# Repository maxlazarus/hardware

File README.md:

#<a href="http://OpenRobotics.ca">OpenRobotics</a> electrical hardware repository<br>
Any questions please contact me at me max.prokopenko@gmail.com<br>
###Organization of this repo<br>
&nbsp;&nbsp;<a href="../../tree/master/Datasheets/">**Datasheets/**</a> Information regarding various components used in our devices<br>
&nbsp;&nbsp;<a href="../../tree/master/Documents/">**Documents/**</a> Reference documents and other useful guides<br>
&nbsp;&nbsp;<a href="../../tree/master/Libraries/">**Libraries/**</a> Device symbols and footprints for electical CAD programs, old ones are in Altium formats, using KiCad going forward<br>
&nbsp;&nbsp;<a href="../../tree/master/Projects/">**Projects/**</a> Contains subfolders, each one dedicated to a single project<br>
&nbsp;&nbsp;<a href="../../tree/master/Training/">**Training/**</a> Training modules developed by OpenRobotics members<br>

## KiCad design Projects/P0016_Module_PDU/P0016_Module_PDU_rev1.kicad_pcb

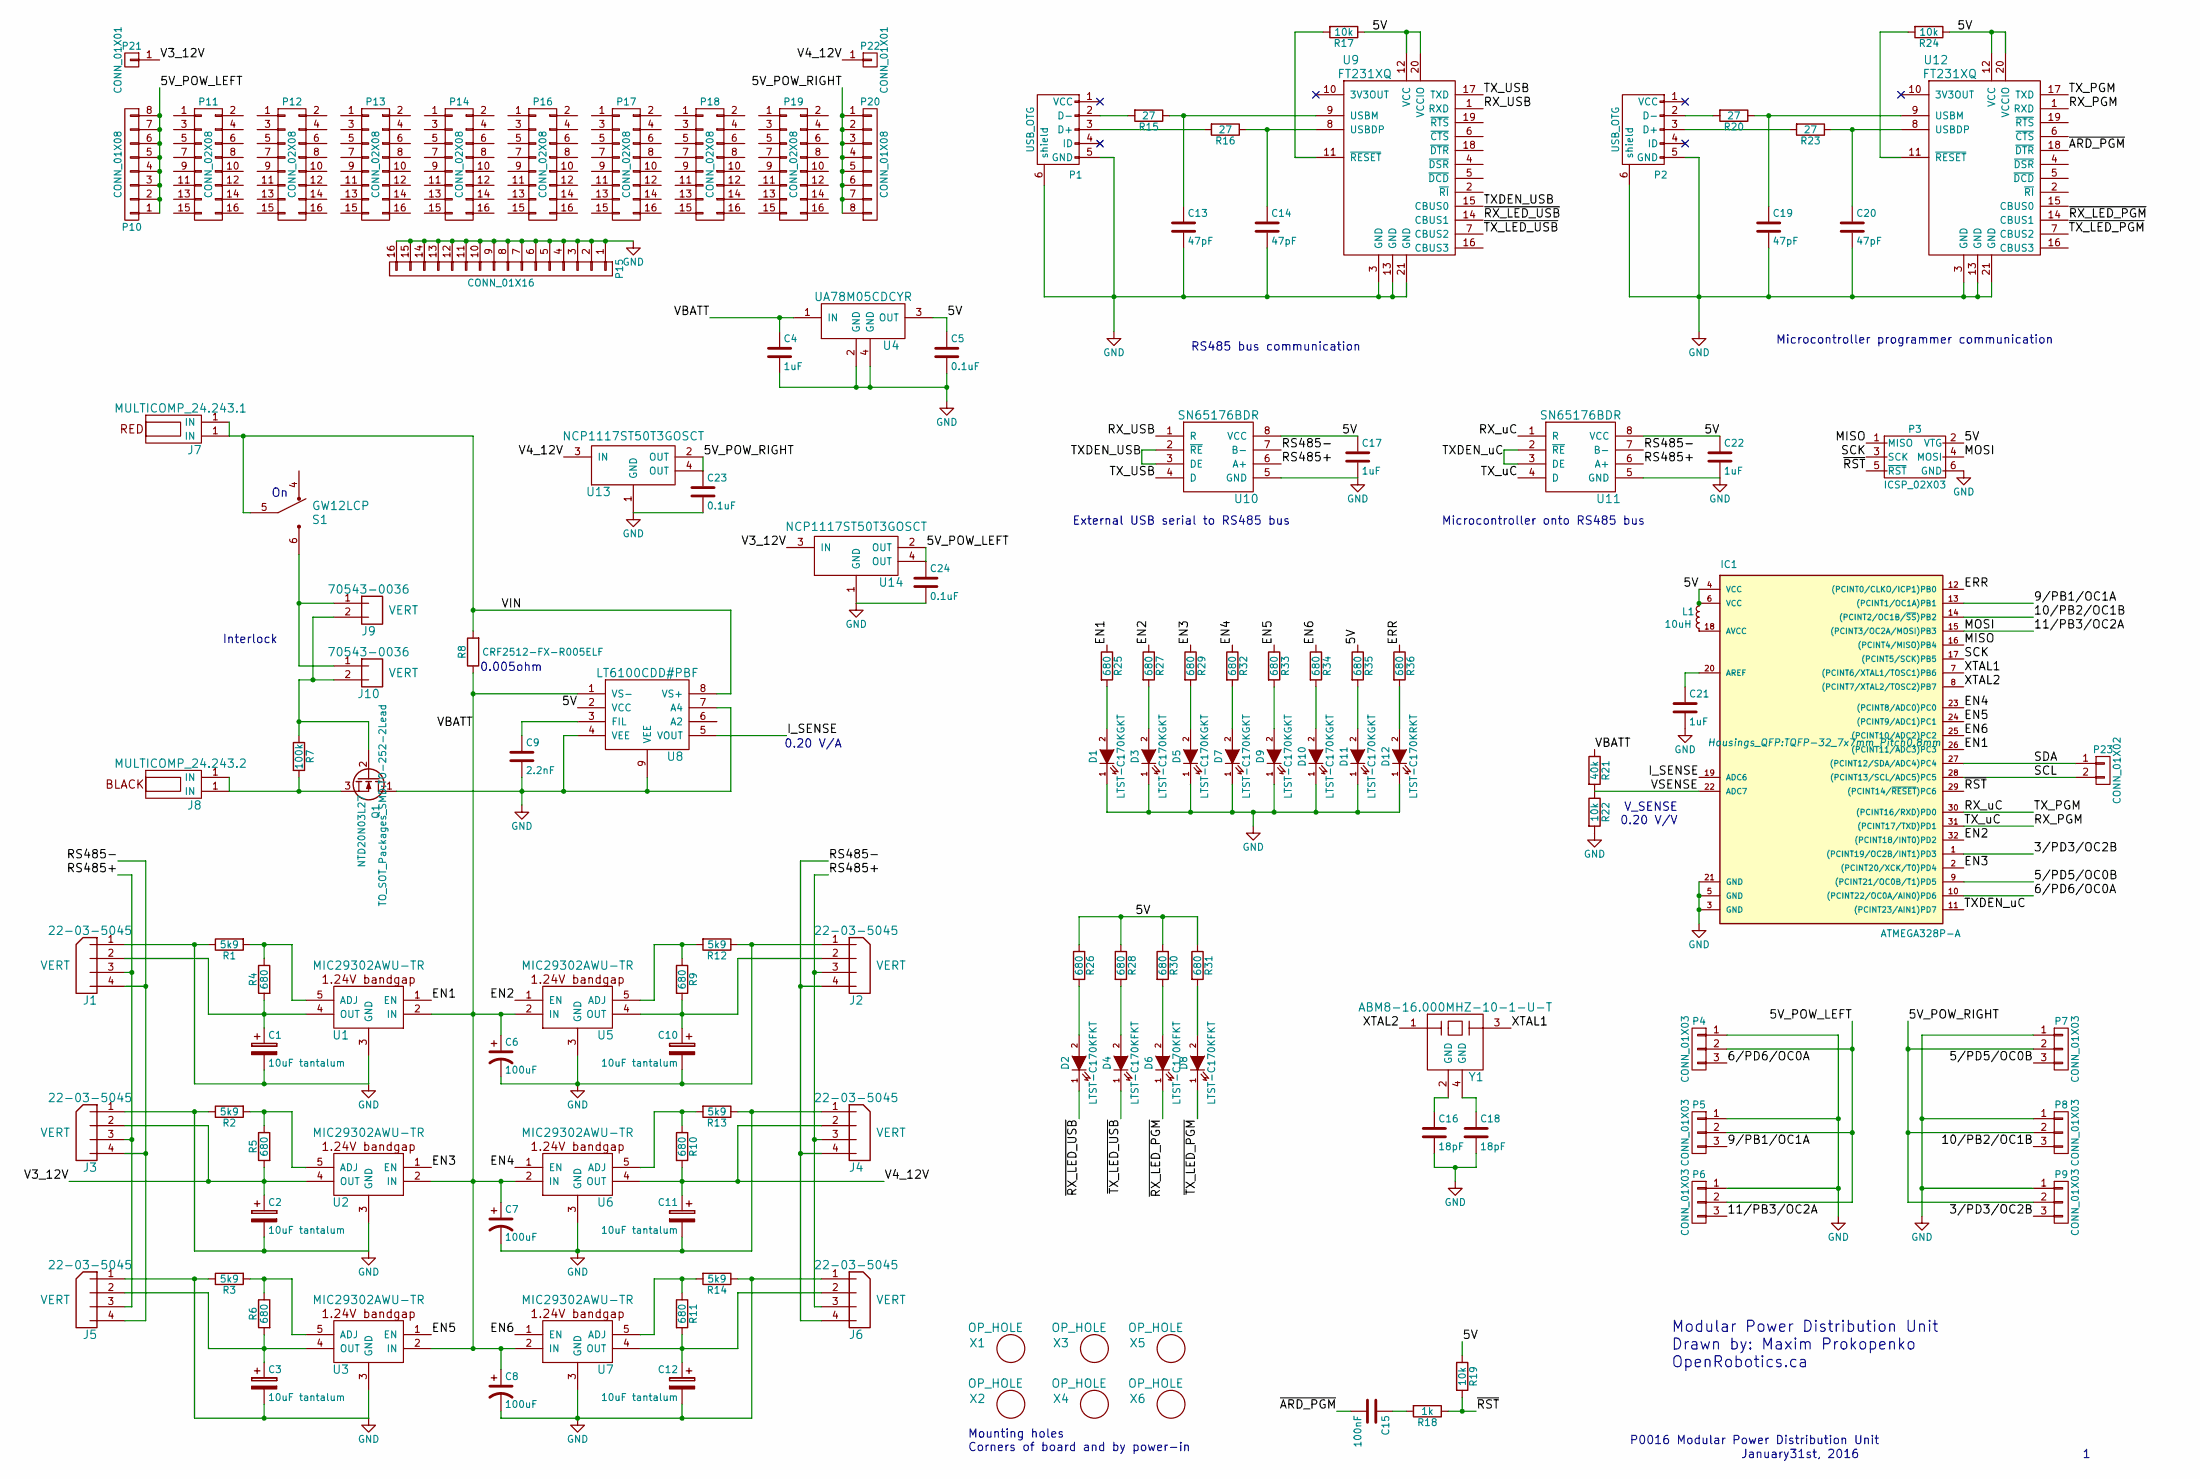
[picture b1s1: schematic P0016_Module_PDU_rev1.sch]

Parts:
C1, C2, C3, C10, C11, C12: 10uF tantalum; c_elec_5x4.5
C4, C17, C21, C22: 1uF; C_0805
C5, C23, C24: 0.1uF; C_0805
C6, C7, C8: 100uF; c_elec_5x4.5
C9: 2.2nF; C_0805
C13, C14, C19, C20: 47pF; C_0805
C15: 100nF; C_0805
C16, C18: 18pF; C_0805
D1, D3, D5, D7, D9, D10, D11: LTST-C170KGKT; LED_0805
D2, D4, D6, D8: LTST-C170KFKT; LED_0805
D12: LTST-C170KRKT; LED_0805
IC1: ATMEGA328P-A; TQFP-32_7x7mm_Pitch0.8mm
J1, J2, J3, J4, J5, J6: 22-03-5045; Pin_Header_Straight_1x04
J7: MULTICOMP_24.243.1; MULTICOMP_4MM_JACK
J8: MULTICOMP_24.243.2; MULTICOMP_4MM_JACK
J9, J10: 70543-0036; Pin_Header_Straight_1x02
L1: 10uH; C_0603
P1, P2: USB_OTG; USB_Micro-B_10103594-0001LF
P3: ICSP_02X03; Pin_Header_Straight_2x03
P4, P5, P6, P7, P8, P9: CONN_01X03; Pin_Header_Straight_1x03
P10, P20: CONN_01X08; Pin_Header_Straight_1x08
P11, P12, P13, P14, P16, P17, P18, P19: CONN_02X08; Pin_Header_Straight_2x08
P15: CONN_01X16; Pin_Header_Straight_1x16
P21, P22: CONN_01X01; Pin_Header_Straight_1x01
P23: CONN_01X02; Pin_Header_Straight_1x02
Q1: NTD20N03L27; TO-252-2Lead
R1, R2, R3, R12, R13, R14: 5k9; R_0603
R4, R5, R6, R9, R10, R11, R25, R26, R27, R28, R29, R30, R31, R32, R33, R34, R35, R36: 680; R_0603
R7: 100k; R_0603
R8: CRF2512-FX-R005ELF; R_2512
R15, R16, R20, R23: 27; R_0603
R17, R19, R22, R24: 10k; R_0603
R18: 1k; R_0603
R21: 40k; R_0603
S1: GW12LCP; GW12LCP_SWITCH_SPDT
U1, U2, U3, U5, U6, U7: MIC29302AWU-TR; TO-263-5Lead
U4: UA78M05CDCYR; SOT-223
U8: LT6100CDD#PBF; DFN-8-1EP_3x3mm_Pitch0.5mm
U9, U12: FT231XQ; QFN-20-1EP_4x4mm_Pitch0.5mm
U10, U11: SN65176BDR; SOIC-8_3.9x4.9mm_Pitch1.27mm
U13, U14: NCP1117ST50T3GOSCT; SOT-223
X1, X2, X3, X4, X5, X6: OP_HOLE; modular8_mounting_hole
Y1: ABM8-16.000MHZ-10-1-U-T; CSMD-ABM8

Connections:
/3/PD3/OC2B: IC1.1 ((PCINT19/OC2B/INT1)PD3), P9.3
/5/PD5/OC0B: IC1.9 ((PCINT21/OC0B/T1)PD5), P7.3
/5V: C5.1, C17.1, C22.1, IC1.4 (VCC), IC1.6 (VCC), L1.1, P3.2 (VTG), R17.1, R19.1, R24.1, R26.1, R28.1, R30.1, R31.1, R35.1, U4.3 (OUT), U8.2 (VCC), U9.12 (VCC), U9.20 (VCCIO), U10.8 (VCC), U11.8 (VCC), U12.12 (VCC), U12.20 (VCCIO)
/5V_POW_LEFT: C24.1, P4.2, P5.2, P6.2, P10.1, P10.2, P10.3, P10.4, P10.5, P10.6, P10.7, P10.8, U14.2 (OUT), U14.4 (OUT)
/5V_POW_RIGHT: C23.1, P7.2, P8.2, P9.2, P20.1, P20.2, P20.3, P20.4, P20.5, P20.6, P20.7, P20.8, U13.2 (OUT), U13.4 (OUT)
/6/PD6/OC0A: IC1.10 ((PCINT22/OC0A/AIN0)PD6), P4.3
/9/PB1/OC1A: IC1.13 ((PCINT1/OC1A)PB1), P5.3
/10/PB2/OC1B: IC1.14 ((PCINT2/OC1B/~SS~)PB2), P8.3
/11/PB3/OC2A: IC1.15 ((PCINT3/OC2A/MOSI)PB3), P3.4 (MOSI), P6.3
/EN1: IC1.26 ((PCINT11/ADC3)PC3), R25.1, U1.1 (EN)
/EN2: IC1.32 ((PCINT18/INT0)PD2), R27.1, U5.1 (EN)
/EN3: IC1.2 ((PCINT20/XCK/T0)PD4), R29.1, U2.1 (EN)
/EN4: IC1.23 ((PCINT8/ADC0)PC0), R32.1, U6.1 (EN)
/EN5: IC1.24 ((PCINT9/ADC1)PC1), R33.1, U3.1 (EN)
/EN6: IC1.25 ((PCINT10/ADC2)PC2), R34.1, U7.1 (EN)
/ERR: IC1.12 ((PCINT0/CLKO/ICP1)PB0), R36.1
/I_SENSE: IC1.19 (ADC6), U8.5 (VOUT)
/MISO: IC1.16 ((PCINT4/MISO)PB4), P3.1 (MISO)
/RS485+: J1.3, J2.3, J3.3, J4.3, J5.3, J6.3, U10.6 (A+), U11.6 (A+)
/RS485-: J1.4, J2.4, J3.4, J4.4, J5.4, J6.4, U10.7 (B-), U11.7 (B-)
/RX_PGM: IC1.31 ((PCINT17/TXD)PD1), U11.4 (D), U12.1 (RXD)
/RX_USB: U9.1 (RXD), U10.1 (R)
/RX_uC: IC1.30 ((PCINT16/RXD)PD0), U11.1 (R), U12.17 (TXD)
/SCK: IC1.17 ((PCINT5/SCK)PB5), P3.3 (SCK)
/SCL: IC1.28 ((PCINT13/SCL/ADC5)PC5), P23.2
/SDA: IC1.27 ((PCINT12/SDA/ADC4)PC4), P23.1
/TXDEN_USB: U9.15 (CBUS0), U10.2 (~RE), U10.3 (DE)
/TXDEN_uC: IC1.11 ((PCINT23/AIN1)PD7), U11.2 (~RE), U11.3 (DE)
/TX_USB: U9.17 (TXD), U10.4 (D)
/V3_12V: C2.1, J3.2, P21.1, R5.2, U2.4 (OUT), U14.3 (IN)
/V4_12V: C11.1, J4.2, P22.1, R10.2, U6.4 (OUT), U13.3 (IN)
/VBATT: C4.1, C6.1, C7.1, C8.1, R8.1, R21.1, U1.2 (IN), U2.2 (IN), U3.2 (IN), U4.1 (IN), U5.2 (IN), U6.2 (IN), U7.2 (IN), U8.1 (VS-)
/VIN: J7.1, R8.2, S1.5, U8.8 (VS+)
/VSENSE: IC1.22 (ADC7), R21.2, R22.1
/XTAL1: IC1.7 ((PCINT6/XTAL1/TOSC1)PB6), Y1.3
/XTAL2: IC1.8 ((PCINT7/XTAL2/TOSC2)PB7), Y1.1
/~ARD_PGM: C15.2, U12.18 (~DTR)
/~RST: IC1.29 ((PCINT14/~RESET~)PC6), P3.5 (~RST), R18.1, R19.2
/~RX_LED_PGM: D6.1 (K), U12.14 (CBUS1)
/~RX_LED_USB: D2.1 (K), U9.14 (CBUS1)
/~TX_LED_PGM: D8.1 (K), U12.7 (CBUS2)
/~TX_LED_USB: D4.1 (K), U9.7 (CBUS2)
GND: C1.2, C2.2, C3.2, C4.2, C5.2, C6.2, C7.2, C8.2, C9.2, C10.2, C11.2, C12.2, C13.2, C14.2, C16.2, C17.2, C18.2, C19.2, C20.2, C21.2, C22.2, C23.2, C24.2, D1.1 (K), D3.1 (K), D5.1 (K), D7.1 (K), D9.1 (K), D10.1 (K), D11.1 (K), D12.1 (K), IC1.3 (GND), IC1.5 (GND), IC1.21 (GND), J1.1, J2.1, J3.1, J4.1, J5.1, J6.1, P1.5 (GND), P1.6 (shield), P2.5 (GND), P2.6 (shield), P3.6 (GND), P4.1, P5.1, P6.1, P7.1, P8.1, P9.1, P15.1, P15.2, P15.3, P15.4, P15.5, P15.6, P15.7, P15.8, P15.9, P15.10, P15.11, P15.12, P15.13, P15.14, P15.15, P15.16, Q1.1 (D), R1.1, R2.1, R3.1, R12.1, R13.1, R14.1, R22.2, U1.3 (GND), U2.3 (GND), U3.3 (GND), U4.2 (GND), U4.4 (GND), U5.3 (GND), U6.3 (GND), U7.3 (GND), U8.4 (VEE), U8.7 (A4), U8.9 (VEE), U9.3 (GND), U9.13 (GND), U9.21 (GND), U10.5 (GND), U11.5 (GND), U12.3 (GND), U12.13 (GND), U12.21 (GND), U13.1 (GND), U14.1 (GND)
unnamed: C1.1, J1.2, R4.2, U1.4 (OUT)
unnamed: C3.1, J5.2, R6.2, U3.4 (OUT)
unnamed: C9.1, U8.3 (FIL)
unnamed: C10.1, J2.2, R9.2, U5.4 (OUT)
unnamed: C12.1, J6.2, R11.2, U7.4 (OUT)
unnamed: C13.1, R15.1, U9.9 (USBM)
unnamed: C14.1, R16.1, U9.8 (USBDP)
unnamed: C15.1, R18.2
unnamed: C16.1, Y1.2 (GND)
unnamed: C18.1, Y1.4 (GND)
unnamed: C19.1, R20.1, U12.9 (USBM)
unnamed: C20.1, R23.1, U12.8 (USBDP)
unnamed: C21.1, IC1.20 (AREF)
unnamed: D1.2 (A), R25.2
unnamed: D2.2 (A), R26.2
unnamed: D3.2 (A), R27.2
unnamed: D4.2 (A), R28.2
unnamed: D5.2 (A), R29.2
unnamed: D6.2 (A), R30.2
unnamed: D7.2 (A), R32.2
unnamed: D8.2 (A), R31.2
unnamed: D9.2 (A), R33.2
unnamed: D10.2 (A), R34.2
unnamed: D11.2 (A), R35.2
unnamed: D12.2 (A), R36.2
unnamed: IC1.18 (AVCC), L1.2
unnamed: J8.1, Q1.3 (S), R7.2
unnamed: J9.1, J10.1, S1.6
unnamed: J9.2, J10.2, Q1.2 (G), R7.1
unnamed: P1.2 (D-), R15.2
unnamed: P1.3 (D+), R16.2
unnamed: P2.2 (D-), R20.2
unnamed: P2.3 (D+), R23.2
unnamed: R1.2, R4.1, U1.5 (ADJ)
unnamed: R2.2, R5.1, U2.5 (ADJ)
unnamed: R3.2, R6.1, U3.5 (ADJ)
unnamed: R10.1, R13.2, U6.5 (ADJ)
unnamed: R11.1, R14.2, U7.5 (ADJ)
unnamed: R9.1, R12.2, U5.5 (ADJ)
unnamed: R17.2, U9.11 (~RESET)
unnamed: R24.2, U12.11 (~RESET)

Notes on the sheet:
P0016 Modular Power Distribution Unit
January31st, 2016
Modular Power Distribution Unit Drawn by: Maxim Prokopenko OpenRobotics.ca
0.20 V/A
0.005ohm
Interlock
V_SENSE 0.20 V/V
Microcontroller programmer communication
RS485 bus communication
Microcontroller onto RS485 bus
External USB serial to RS485 bus
Mounting holes Corners of board and by power-in

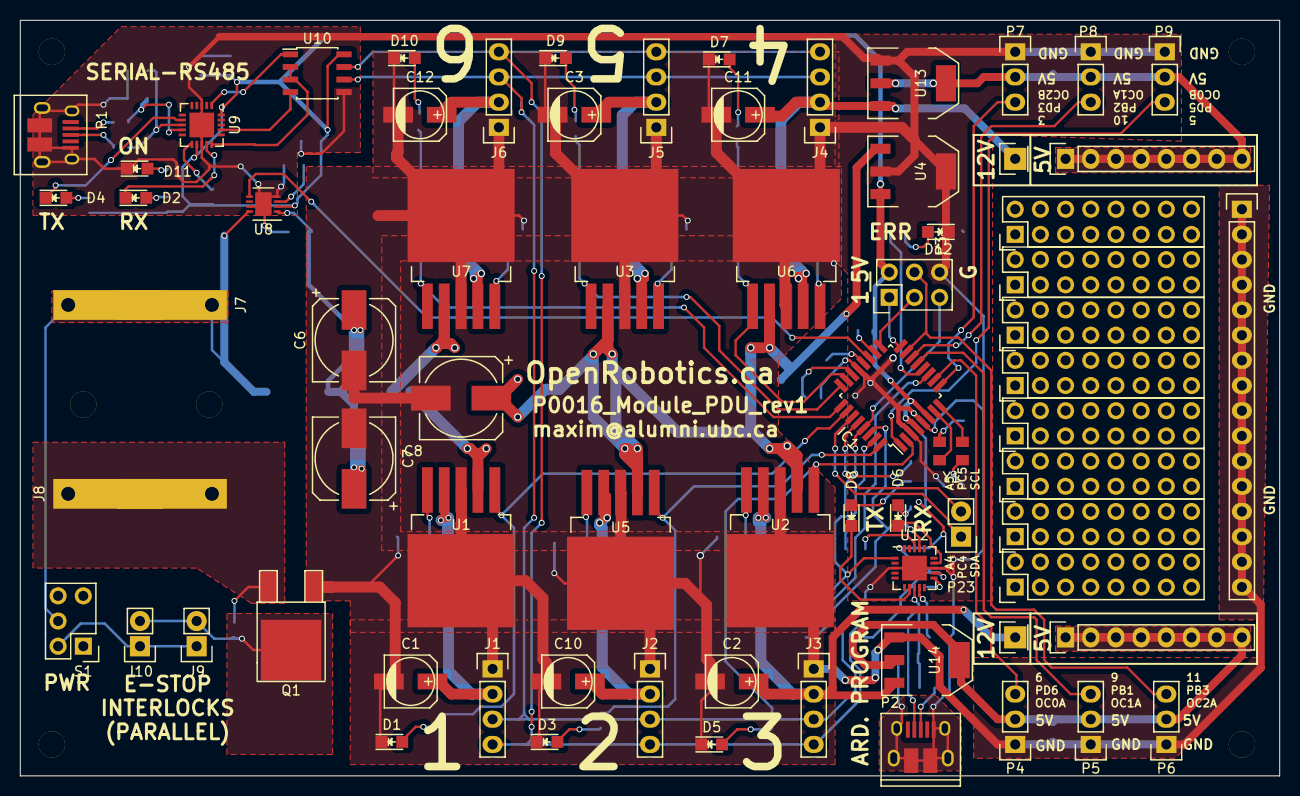
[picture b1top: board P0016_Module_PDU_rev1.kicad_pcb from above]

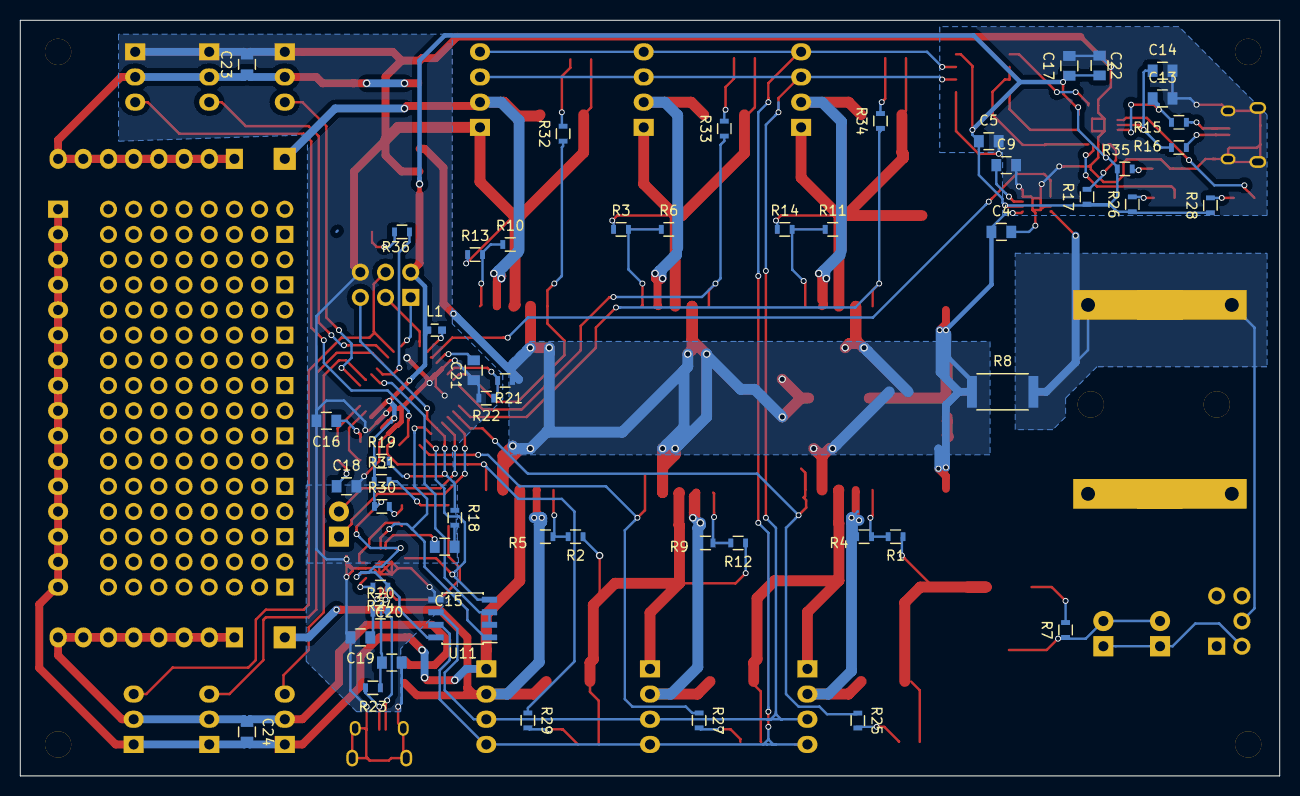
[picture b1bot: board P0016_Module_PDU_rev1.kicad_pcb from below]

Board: 2 copper layers, 127.0 x 76.2 mm, 130 parts (53 on the bottom side), 84 nets.

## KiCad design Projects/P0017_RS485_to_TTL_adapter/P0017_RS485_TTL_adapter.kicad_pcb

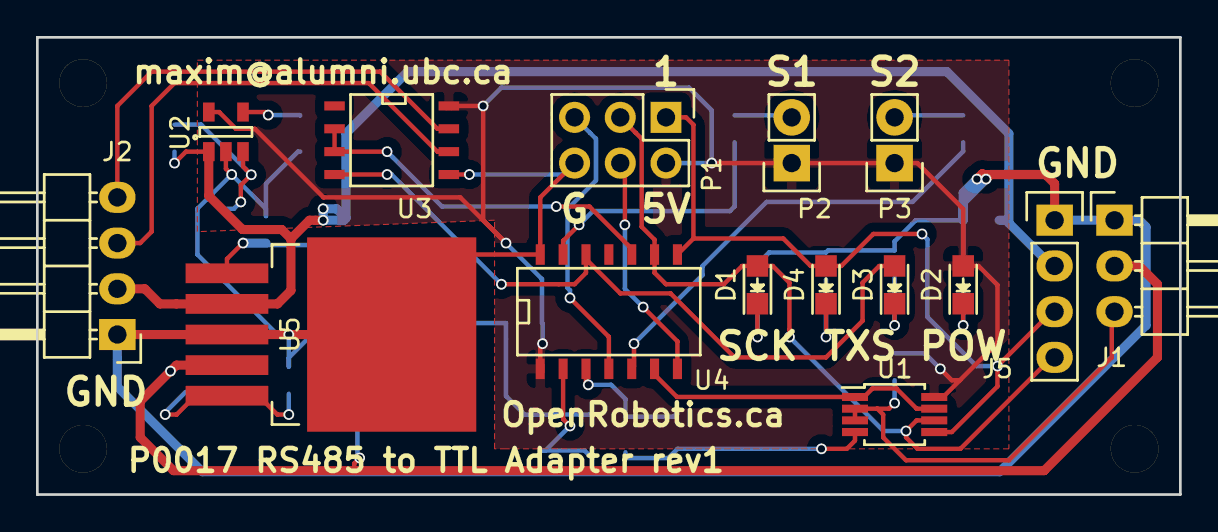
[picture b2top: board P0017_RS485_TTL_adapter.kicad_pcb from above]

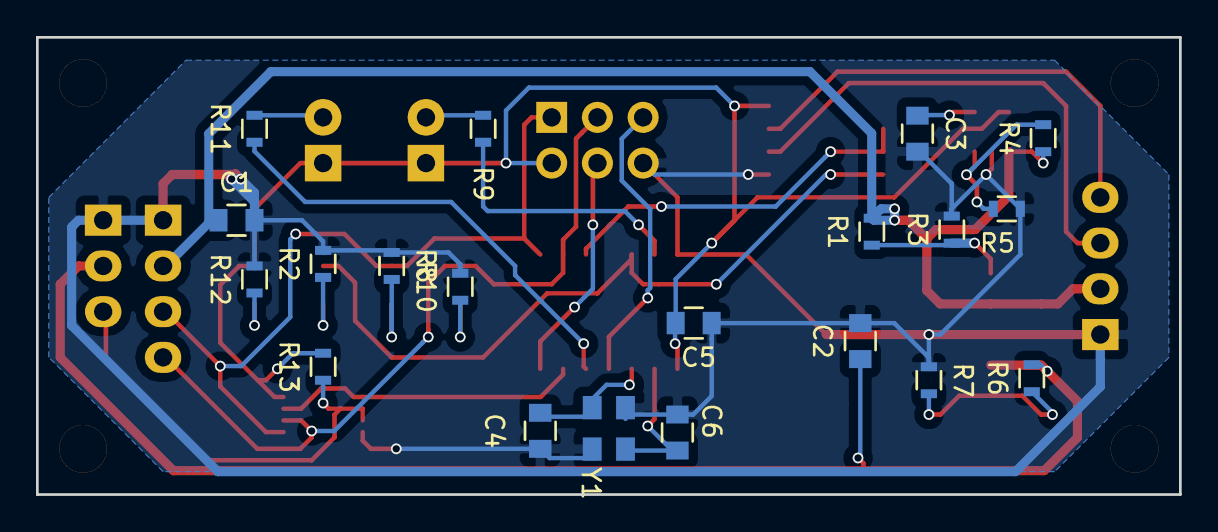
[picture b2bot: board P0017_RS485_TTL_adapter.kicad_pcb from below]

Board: 2 copper layers, 63.5 x 25.4 mm, 39 parts (20 on the bottom side), 28 nets.

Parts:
C1, C2: 10uF; C_0805
C3: 470pF; C_0805
C4, C6: 18pF; C_0805
C5: 4.7uF; C_0805
D1, D3, D4: LTST-C170KFKT; LED_0805
D2: LTST-C170KGKT; LED_0805
J1: 22-05-7035; Pin_Header_Angled_1x03
J2: 22-05-7045; Pin_Header_Angled_1x04
J5: CONN_01X04; Pin_Header_Straight_1x04
P1: CONN_02X03; Pin_Header_Straight_2x03
P2, P3: CONN_01X02; Pin_Header_Straight_1x02
R1, R2, R3, R4, R5, R7, R8, R9, R10, R11, R12: 1k; R_0603
R6: 6.8k; R_0603
R13: 2k4; R_0603
U1: TC7W241FUTE12LF; MSOP-8_3x3mm_Pitch0.65mm
U2: MIC5219-5.0YM5-TR; SOT-23-5
U3: SN65176BDR; SOIC-8-N
U4: ATTINY841-SSU; SOIC-14_N
U5: MIC29302AWU-TR; TO-263-5Lead
X1, X2, X3, X4: OP_HOLE; modular8_mounting_hole
Y1: ABM8-16.000MHZ-10-1-U-T; CSMD-ABM8

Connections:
/5V: C5.1, D2.2, P1.2, P2.1, P3.1, R13.2, U1.8, U2.5, U3.8, U4.1
/9V7: C2.1, J1.2, R6.2, U5.4
/12V: C1.1, J2.2, J5.2, R1.2, R4.1, U2.1, U5.2
/MISO: D4.2, J5.3, P1.1, U1.5, U4.8
/MOSI: P1.4, U4.7
/RS485+: J2.3, U3.6
/RS485-: J2.4, U3.7
/RX_TTL: D1.2, J5.4, P1.3, U1.6, U4.9
/TTL_BUS: J1.3, R13.1, U1.2, U1.3
/TXDEN_RS485: U3.2, U3.3, U4.10
/TXDEN_TTL: U1.1, U1.7, U4.6
/TX_RS485: D3.2, U3.4, U4.12
/~RESET: P1.5, U4.4
GND: C1.2, C2.2, C3.2, C4.2, C5.2, C6.2, J1.1, J2.1, J5.1, P1.6, R2.2, R3.1, R5.2, R7.1, R8.1, R10.2, R12.2, U1.4, U2.2, U3.5, U4.14, U5.3, Y1.2, Y1.4
unnamed: C3.1, U2.4
unnamed: C4.1, U4.3, Y1.1
unnamed: C6.1, U4.2, Y1.3
unnamed: D1.1, R10.1
unnamed: D2.1, R12.1
unnamed: D3.1, R2.1
unnamed: D4.1, R8.2
unnamed: P2.2, R9.1
unnamed: P3.2, R11.2
unnamed: R1.1, R3.2, U5.1
unnamed: R4.2, R5.1, U2.3
unnamed: R6.1, R7.2, U5.5
unnamed: R9.2, U4.13
unnamed: R11.1, U4.5

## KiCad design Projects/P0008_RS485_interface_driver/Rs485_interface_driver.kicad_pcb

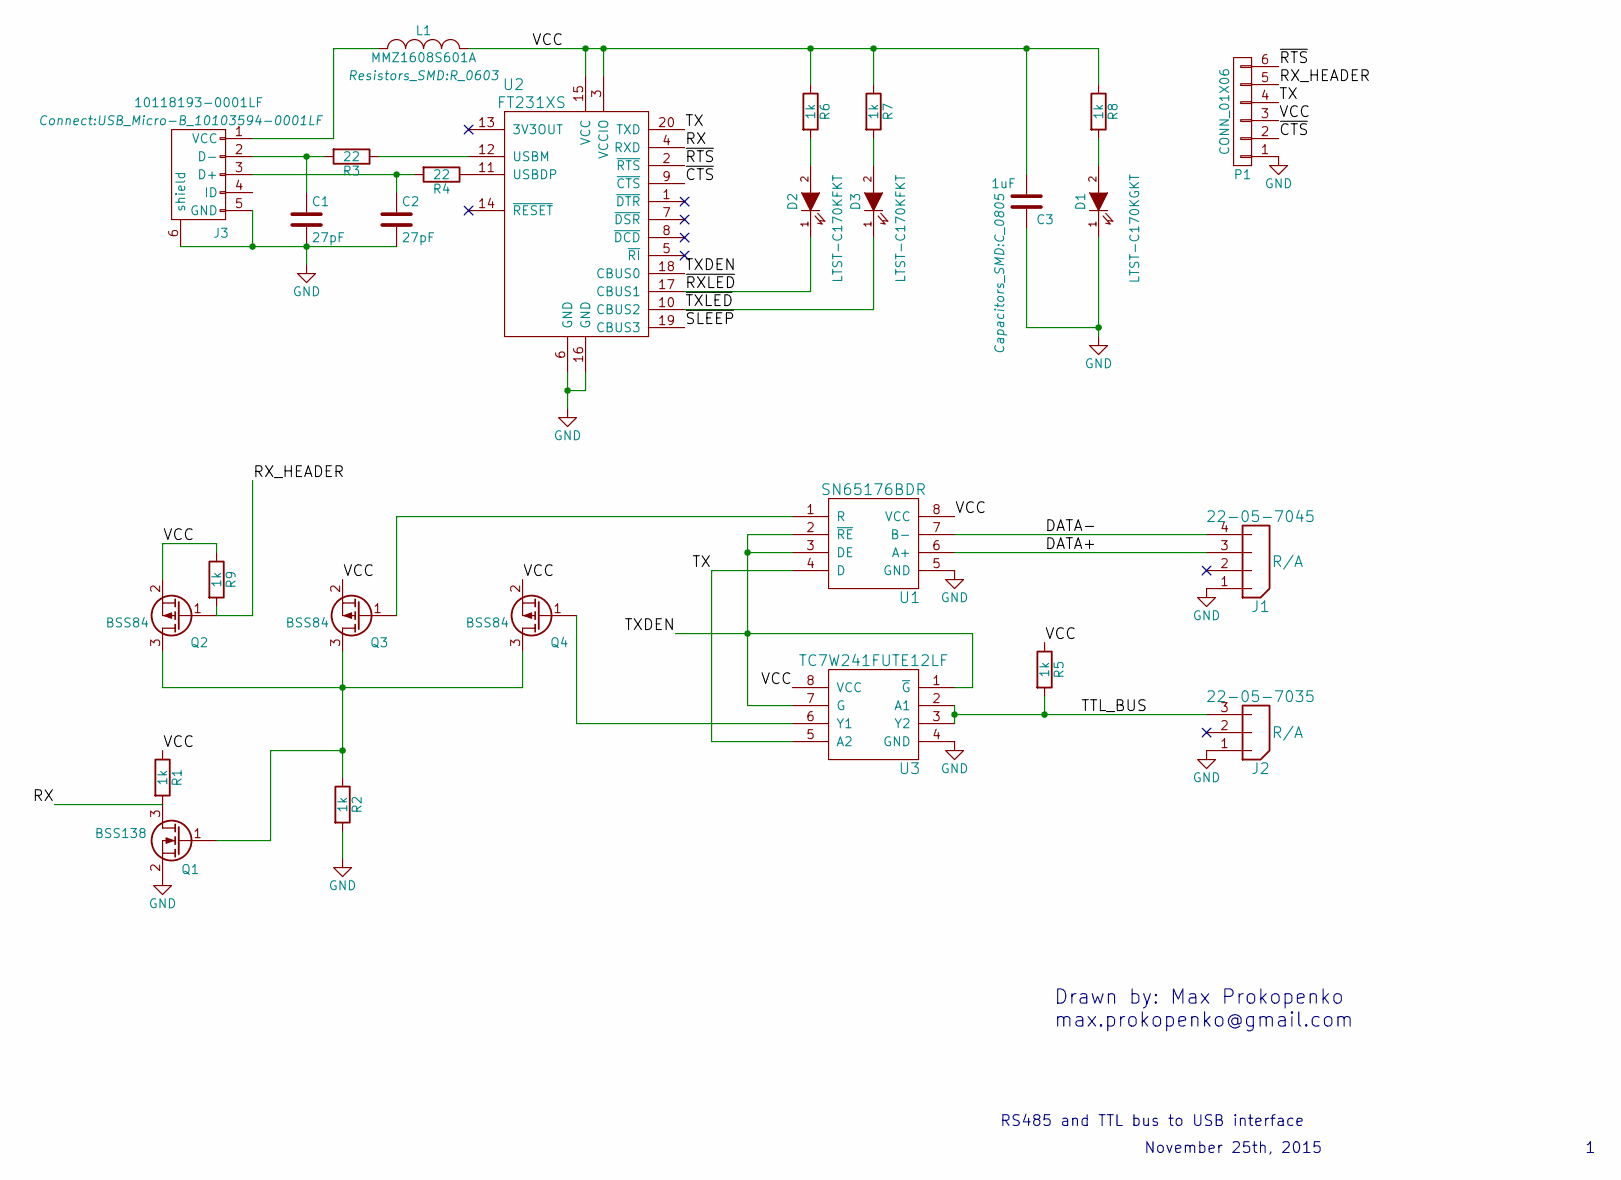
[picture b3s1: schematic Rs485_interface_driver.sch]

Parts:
C1, C2: 27pF; C_0402
C3: 1uF; C_0805
D1: LTST-C170KGKT; LED_0805
D2, D3: LTST-C170KFKT; LED_0805
J1: 22-05-7045; Pin_Header_Angled_1x04
J2: 22-05-7035; Pin_Header_Angled_1x03
J3: 10118193-0001LF; USB_Micro-B_10103594-0001LF
L1: MMZ1608S601A; R_0603
P1: CONN_01X06; Pin_Header_Straight_1x06
Q1: BSS138; SOT-23
Q2, Q3, Q4: BSS84; SOT-23
R1, R2, R5, R6, R7, R8, R9: 1k; R_0805
R3, R4: 22; R_0805
U1: SN65176BDR; SOIC-8_3.9x4.9mm_Pitch1.27mm
U2: FT231XS; SSOP-20
U3: TC7W241FUTE12LF; MSOP-8_3x3mm_Pitch0.65mm

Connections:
/DATA+: J1.3, U1.6 (A+)
/DATA-: J1.4, U1.7 (B-)
/RX: Q1.3 (D), R1.2, U2.4 (RXD)
/RX_HEADER: P1.5, Q2.1 (G), R9.2
/TTL_BUS: J2.3, R5.2, U3.2 (A1), U3.3 (Y2)
/TX: P1.4, U1.4 (D), U2.20 (TXD), U3.5 (A2)
/TXDEN: U1.2 (~RE), U1.3 (DE), U2.18 (CBUS0), U3.1 (~G), U3.7 (G)
/VCC: C3.1, L1.2, P1.3, Q2.2 (S), Q3.2 (S), Q4.2 (S), R1.1, R5.1, R6.1, R7.1, R8.1, R9.1, U1.8 (VCC), U2.3 (VCCIO), U2.15 (VCC), U3.8 (VCC)
/~CTS: P1.2, U2.9 (~CTS)
/~RTS: P1.6, U2.2 (~RTS)
/~RXLED: D2.1 (K), U2.17 (CBUS1)
/~TXLED: D3.1 (K), U2.10 (CBUS2)
GND: C1.2, C2.2, C3.2, D1.1 (K), J1.1, J2.1, J3.5 (GND), J3.6 (shield), P1.1, Q1.2 (S), R2.2, U1.5 (GND), U2.6 (GND), U2.16 (GND), U3.4 (GND)
unnamed: C1.1, J3.2 (D-), R3.2
unnamed: C2.1, J3.3 (D+), R4.2
unnamed: D1.2 (A), R8.2
unnamed: D2.2 (A), R6.2
unnamed: D3.2 (A), R7.2
unnamed: J3.1 (VCC), L1.1
unnamed: Q1.1 (G), Q2.3 (D), Q3.3 (D), Q4.3 (D), R2.1
unnamed: Q3.1 (G), U1.1 (R)
unnamed: Q4.1 (G), U3.6 (Y1)
unnamed: R3.1, U2.12 (USBM)
unnamed: R4.1, U2.11 (USBDP)

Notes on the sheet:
RS485 and TTL bus to USB interface
November 25th, 2015
Drawn by: Max Prokopenko max.prokopenko@gmail.com

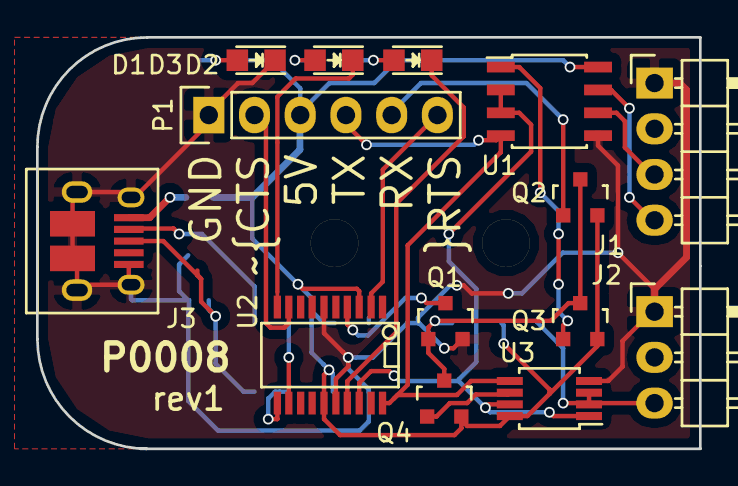
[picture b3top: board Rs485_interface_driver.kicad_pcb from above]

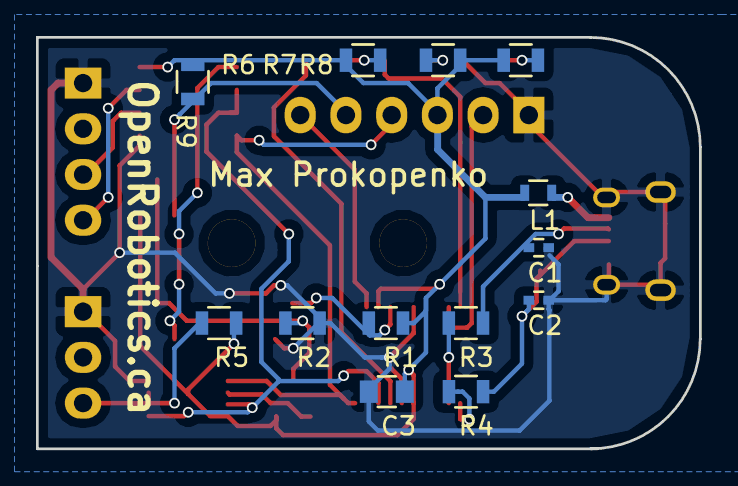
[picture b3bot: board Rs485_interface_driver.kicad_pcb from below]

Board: 2 copper layers, 36.8 x 22.9 mm, 27 parts (13 on the bottom side), 24 nets.

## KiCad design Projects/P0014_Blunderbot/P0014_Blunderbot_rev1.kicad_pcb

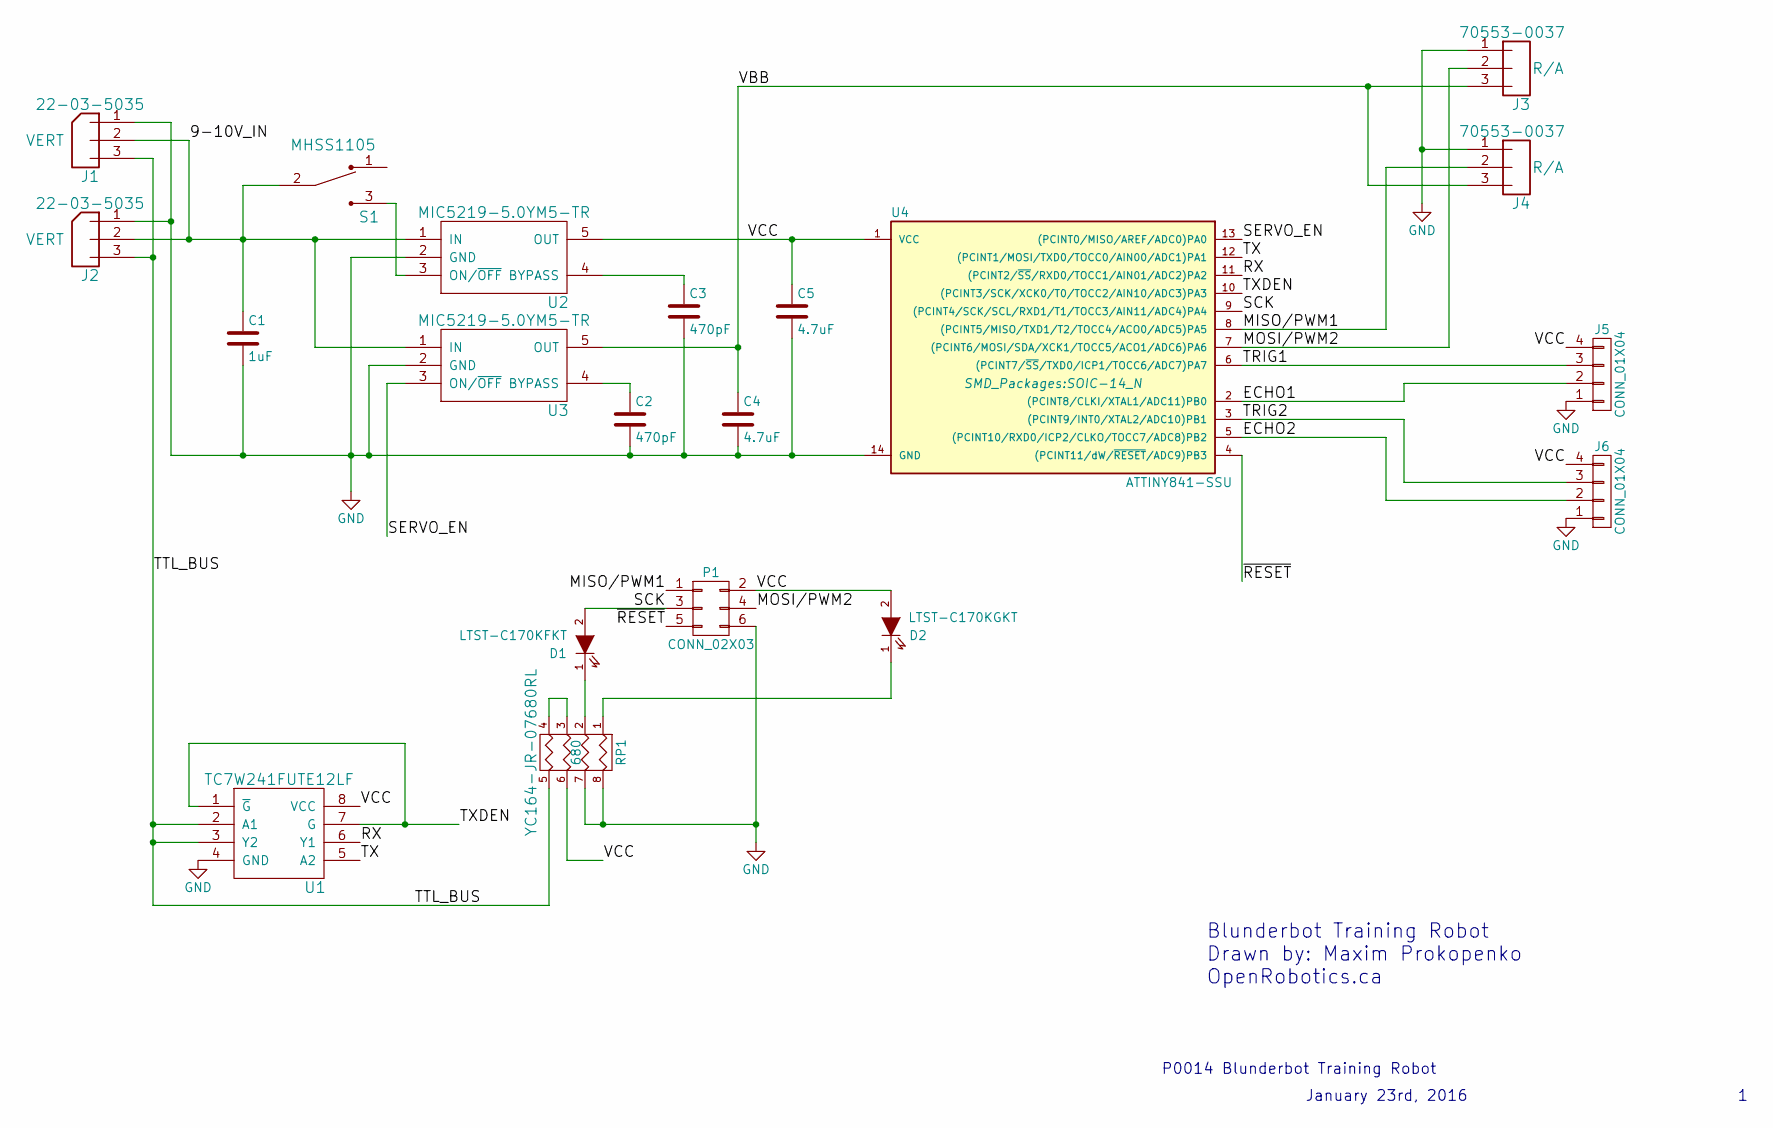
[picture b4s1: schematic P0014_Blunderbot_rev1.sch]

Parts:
C1: 1uF; C_0805_HandSoldering
C2, C3: 470pF; C_0805_HandSoldering
C4, C5: 4.7uF; C_0805_HandSoldering
D1: LTST-C170KFKT; LED_0805
D2: LTST-C170KGKT; LED_0805
J1, J2: 22-03-5035; Pin_Header_Straight_1x03
J3, J4: 70553-0037; Pin_Header_Angled_1x03
J5, J6: CONN_01X04; Pin_Header_Straight_1x04
P1: CONN_02X03; Pin_Header_Straight_2x03
RP1: 680; R_Array_Convex_4x1206; Part1 YC164-JR-07680RL
S1: MHSS1105; Pin_Header_Straight_1x03
U1: TC7W241FUTE12LF; MSOP-8_3x3mm_Pitch0.65mm
U2, U3: MIC5219-5.0YM5-TR; SOT-23-5
U4: ATTINY841-SSU; SOIC-14_N

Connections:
/9-10V_IN: C1.1, J1.2, J2.2, S1.2, U2.1 (IN), U3.1 (IN)
/ECHO1: J5.2, U4.2 ((PCINT8/CLKI/XTAL1/ADC11)PB0)
/ECHO2: J6.2, U4.5 ((PCINT10/RXD0/ICP2/CLKO/TOCC7/ADC8)PB2)
/MISO/PWM1: J4.2, P1.1, U4.8 ((PCINT5/MISO/TXD1/T2/TOCC4/ACO0/ADC5)PA5)
/MOSI/PWM2: J3.2, P1.4, U4.7 ((PCINT6/MOSI/SDA/XCK1/TOCC5/ACO1/ADC6)P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)
/RX: U1.6 (Y1), U4.11 ((PCINT2/~SS~/RXD0/TOCC1/AIN01/ADC2)PA2)
/SCK: D1.2 (A), P1.3, U4.9 ((PCINT4/SCK/SCL/RXD1/T1/TOCC3/AIN11/ADC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)
/SERVO_EN: U3.3 (ON/~OFF), U4.13 ((PCINT0/MISO/AREF/ADC0)PA0)
/TRIG1: J5.3, U4.6 ((PCINT7/~SS~/TXD0/ICP1/TOCC6/ADC7)PA7)
/TRIG2: J6.3, U4.3 ((PCINT9/INT0/XTAL2/ADC10)PB1)
/TTL_BUS: J1.3, J2.3, RP1.5 (R4), U1.2 (A1), U1.3 (Y2)
/TX: U1.5 (A2), U4.12 ((PCINT1/MOSI/TXD0/TOCC0/AIN00/ADC1)PA1)
/TXDEN: U1.1 (~G), U1.7 (G), U4.10 ((PCINT3/SCK/XCK0/T0/TOCC2/AIN10/ADC3)PA3)
/VBB: C4.1, J3.3, J4.3, U3.5 (OUT)
/VCC: C5.1, D2.2 (A), J5.4, J6.4, P1.2, RP1.6 (R3), U1.8 (VCC), U2.5 (OUT), U4.1 (VCC)
/~RESET: P1.5, U4.4 ((PCINT11/dW/~RESET~/ADC9)PB3)
GND: C1.2, C2.2, C3.2, C4.2, C5.2, J1.1, J2.1, J3.1, J4.1, J5.1, J6.1, P1.6, RP1.7 (R2), RP1.8 (R1), U1.4 (GND), U2.2 (GND), U3.2 (GND), U4.14 (GND)
unnamed: C2.1, U3.4 (BYPASS)
unnamed: C3.1, U2.4 (BYPASS)
unnamed: D1.1 (K), RP1.2
unnamed: D2.1 (K), RP1.1
unnamed: RP1.3, RP1.4
unnamed: S1.3, U2.3 (ON/~OFF)

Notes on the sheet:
P0014 Blunderbot Training Robot
January 23rd, 2016
Blunderbot Training Robot Drawn by: Maxim Prokopenko OpenRobotics.ca

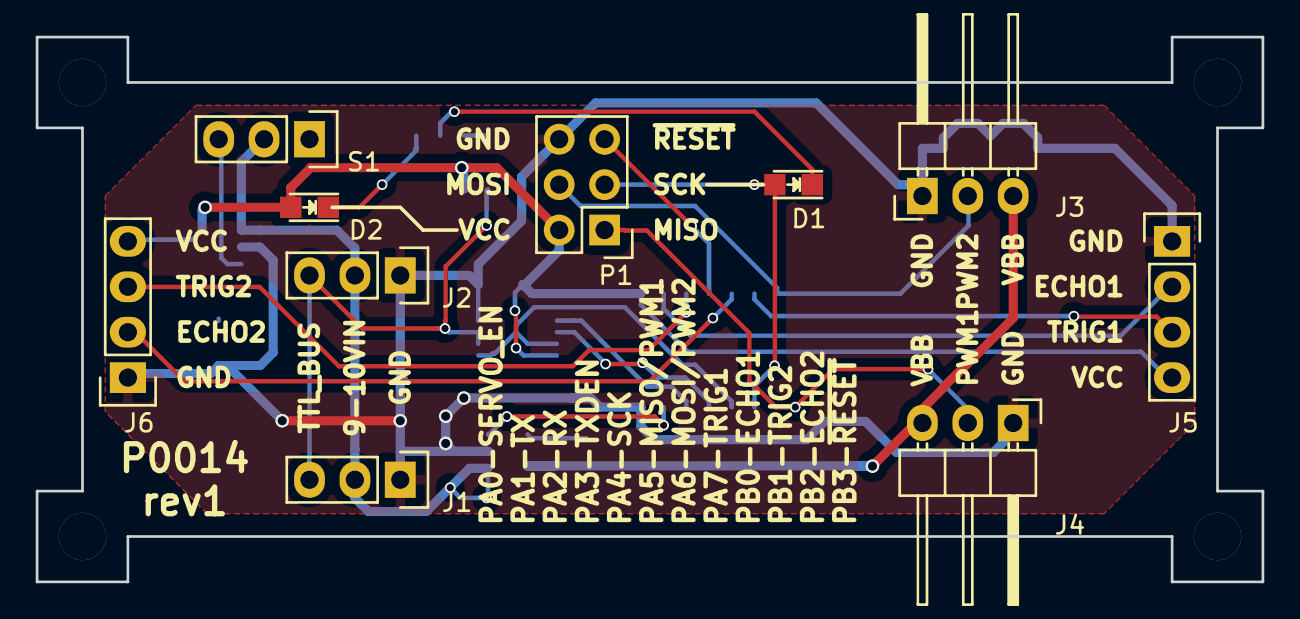
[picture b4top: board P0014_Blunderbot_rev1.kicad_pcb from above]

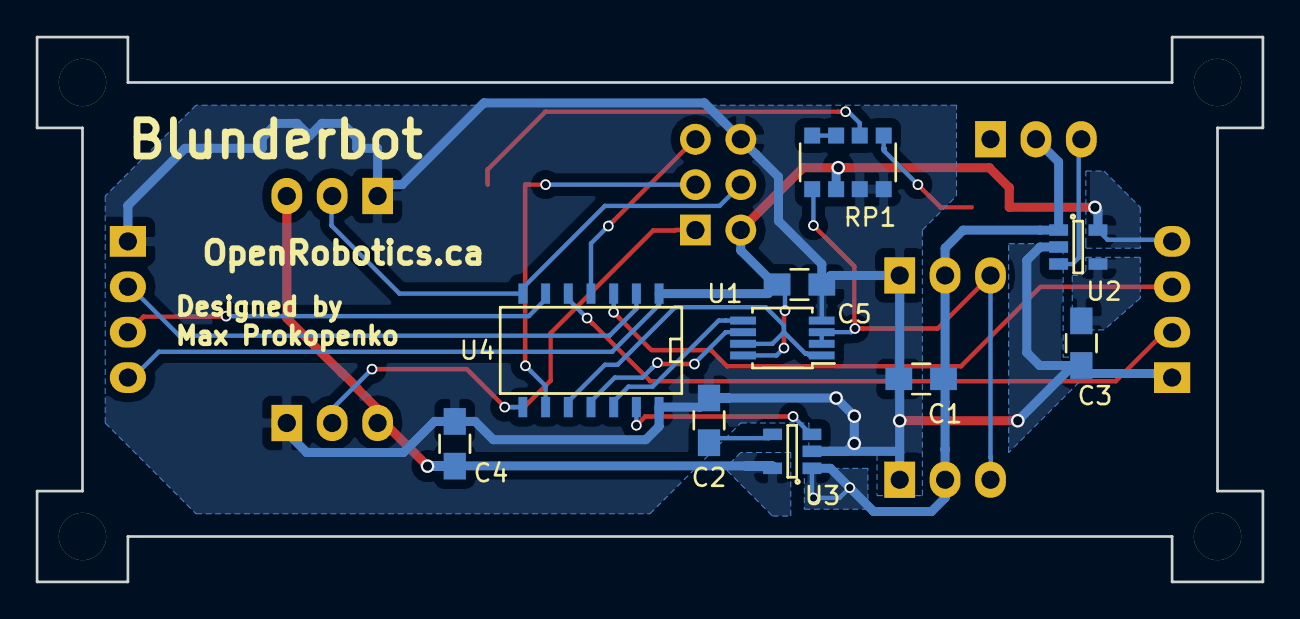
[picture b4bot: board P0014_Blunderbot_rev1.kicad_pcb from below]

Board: 2 copper layers, 68.6 x 30.5 mm, 20 parts (10 on the bottom side), 23 nets.
